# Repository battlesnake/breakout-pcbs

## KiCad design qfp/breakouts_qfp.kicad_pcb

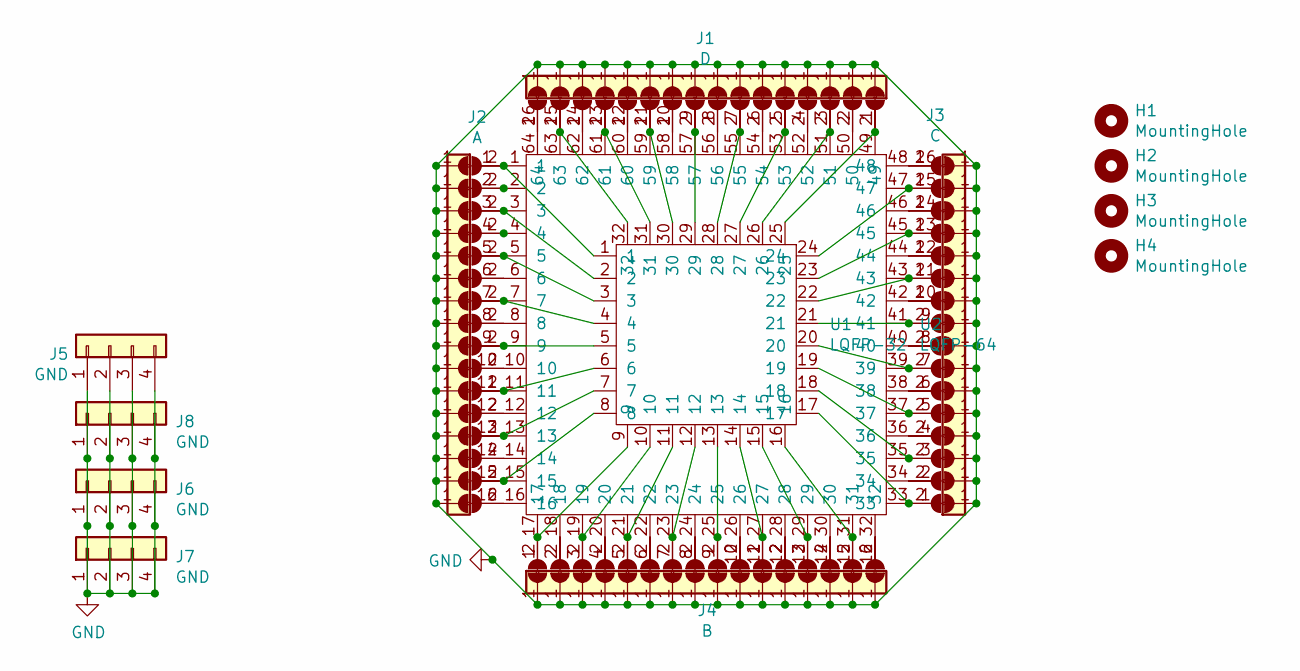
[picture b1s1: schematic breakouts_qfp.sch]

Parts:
H1, H2, H3, H4: MountingHole; MountingHole_2.2mm_M2
J1: D; PinHeader_1x16_P1.27mm_Vertical
J2: A; PinHeader_1x16_P1.27mm_Vertical
J3: C; PinHeader_1x16_P1.27mm_Vertical
J4: B; PinHeader_1x16_P1.27mm_Vertical
J5, J6, J7, J8: GND; PinHeader_1x04_P1.27mm_Vertical
JP1, JP2, JP3, JP4, JP5, JP6, JP7, JP8, JP9, JP10, JP11, JP12, JP13, JP14, JP15, JP16, JP17, JP18, JP19, JP20, JP21, JP22, JP23, JP24, JP25, JP26, JP27, JP28, JP29, JP30, JP31, JP32, JP33, JP34, JP35, JP36, JP37, JP38, JP39, JP40, JP41, JP42, JP43, JP44, JP45, JP46, JP47, JP48, JP49, JP50, JP51, JP52, JP53, JP54, JP55, JP56, JP57, JP58, JP59, JP60, JP61, JP62, JP63, JP64: SolderJumper_2_Open; C_0402_1005Metric_Pad0.74x0.62mm_HandSolder
U1: LQFP-32; LQFP-32_5x5mm_P0.5mm
U2: LQFP-64; LQFP-64_10x10mm_P0.5mm

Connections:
GND: J5.1, J5.2, J5.3, J5.4, J6.1, J6.2, J6.3, J6.4, J7.1, J7.2, J7.3, J7.4, J8.1, J8.2, J8.3, J8.4, JP1.1 (A), JP2.1 (A), JP3.1 (A), JP4.1 (A), JP5.1 (A), JP6.1 (A), JP7.1 (A), JP8.1 (A), JP9.1 (A), JP10.1 (A), JP11.1 (A), JP12.1 (A), JP13.1 (A), JP14.1 (A), JP15.1 (A), JP16.1 (A), JP17.1 (A), JP18.1 (A), JP19.1 (A), JP20.1 (A), JP21.1 (A), JP22.1 (A), JP23.1 (A), JP24.1 (A), JP25.1 (A), JP26.1 (A), JP27.1 (A), JP28.1 (A), JP29.1 (A), JP30.1 (A), JP31.1 (A), JP32.1 (A), JP33.1 (A), JP34.1 (A), JP35.1 (A), JP36.1 (A), JP37.1 (A), JP38.1 (A), JP39.1 (A), JP40.1 (A), JP41.1 (A), JP42.1 (A), JP43.1 (A), JP44.1 (A), JP45.1 (A), JP46.1 (A), JP47.1 (A), JP48.1 (A), JP49.1 (A), JP50.1 (A), JP51.1 (A), JP52.1 (A), JP53.1 (A), JP54.1 (A), JP55.1 (A), JP56.1 (A), JP57.1 (A), JP58.1 (A), JP59.1 (A), JP60.1 (A), JP61.1 (A), JP62.1 (A), JP63.1 (A), JP64.1 (A)
unnamed: J1.1, JP16.2 (B), U1.25, U2.49
unnamed: J1.2, JP15.2 (B), U2.50
unnamed: J1.3, JP14.2 (B), U1.26, U2.51
unnamed: J1.4, JP13.2 (B), U2.52
unnamed: J1.5, JP12.2 (B), U1.27, U2.53
unnamed: J1.6, JP11.2 (B), U2.54
unnamed: J1.7, JP10.2 (B), U1.28, U2.55
unnamed: J1.8, JP9.2 (B), U2.56
unnamed: J1.9, JP8.2 (B), U1.29, U2.57
unnamed: J1.10, JP7.2 (B), U2.58
unnamed: J1.11, JP6.2 (B), U1.30, U2.59
unnamed: J1.12, JP5.2 (B), U2.60
unnamed: J1.13, JP4.2 (B), U1.31, U2.61
unnamed: J1.14, JP3.2 (B), U2.62
unnamed: J1.15, JP2.2 (B), U1.32, U2.63
unnamed: J1.16, JP1.2 (B), U2.64
unnamed: J2.1, JP17.2 (B), U1.1, U2.1
unnamed: J2.2, JP19.2 (B), U2.2
unnamed: J2.3, JP21.2 (B), U1.2, U2.3
unnamed: J2.4, JP23.2 (B), U2.4
unnamed: J2.5, JP25.2 (B), U1.3, U2.5
unnamed: J2.6, JP27.2 (B), U2.6
unnamed: J2.7, JP29.2 (B), U1.4, U2.7
unnamed: J2.8, JP31.2 (B), U2.8
unnamed: J2.9, JP33.2 (B), U1.5, U2.9
unnamed: J2.10, JP35.2 (B), U2.10
unnamed: J2.11, JP37.2 (B), U1.6, U2.11
unnamed: J2.12, JP39.2 (B), U2.12
unnamed: J2.13, JP41.2 (B), U1.7, U2.13
unnamed: J2.14, JP43.2 (B), U2.14
unnamed: J2.15, JP45.2 (B), U1.8, U2.15
unnamed: J2.16, JP47.2 (B), U2.16
unnamed: J3.1, JP48.2 (B), U1.17, U2.33
unnamed: J3.2, JP46.2 (B), U2.34
unnamed: J3.3, JP44.2 (B), U1.18, U2.35
unnamed: J3.4, JP42.2 (B), U2.36
unnamed: J3.5, JP40.2 (B), U1.19, U2.37
unnamed: J3.6, JP38.2 (B), U2.38
unnamed: J3.7, JP36.2 (B), U1.20, U2.39
unnamed: J3.8, JP34.2 (B), U2.40
unnamed: J3.9, JP32.2 (B), U1.21, U2.41
unnamed: J3.10, JP30.2 (B), U2.42
unnamed: J3.11, JP28.2 (B), U1.22, U2.43
unnamed: J3.12, JP26.2 (B), U2.44
unnamed: J3.13, JP24.2 (B), U1.23, U2.45
unnamed: J3.14, JP22.2 (B), U2.46
unnamed: J3.15, JP20.2 (B), U1.24, U2.47
unnamed: J3.16, JP18.2 (B), U2.48
unnamed: J4.1, JP49.2 (B), U1.9, U2.17
unnamed: J4.2, JP50.2 (B), U2.18
unnamed: J4.3, JP51.2 (B), U1.10, U2.19
unnamed: J4.4, JP52.2 (B), U2.20
unnamed: J4.5, JP53.2 (B), U1.11, U2.21
unnamed: J4.6, JP54.2 (B), U2.22
unnamed: J4.7, JP55.2 (B), U1.12, U2.23
unnamed: J4.8, JP56.2 (B), U2.24
unnamed: J4.9, JP57.2 (B), U1.13, U2.25
unnamed: J4.10, JP58.2 (B), U2.26
unnamed: J4.11, JP59.2 (B), U1.14, U2.27
unnamed: J4.12, JP60.2 (B), U2.28
unnamed: J4.13, JP61.2 (B), U1.15, U2.29
unnamed: J4.14, JP62.2 (B), U2.30
unnamed: J4.15, JP63.2 (B), U1.16, U2.31
unnamed: J4.16, JP64.2 (B), U2.32

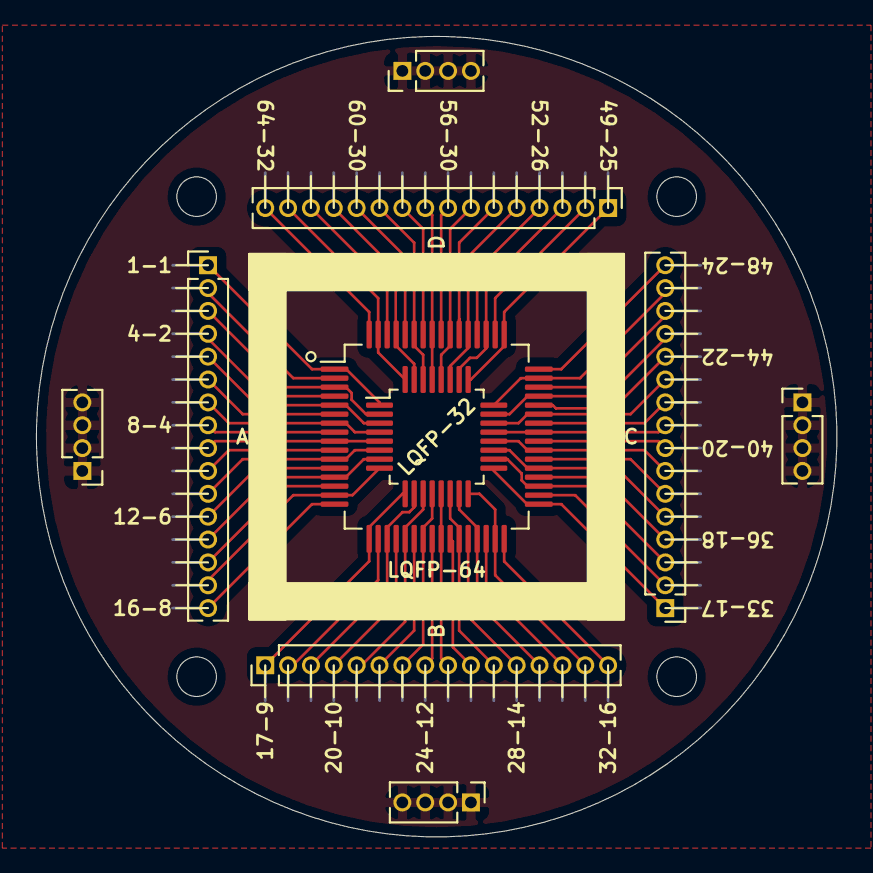
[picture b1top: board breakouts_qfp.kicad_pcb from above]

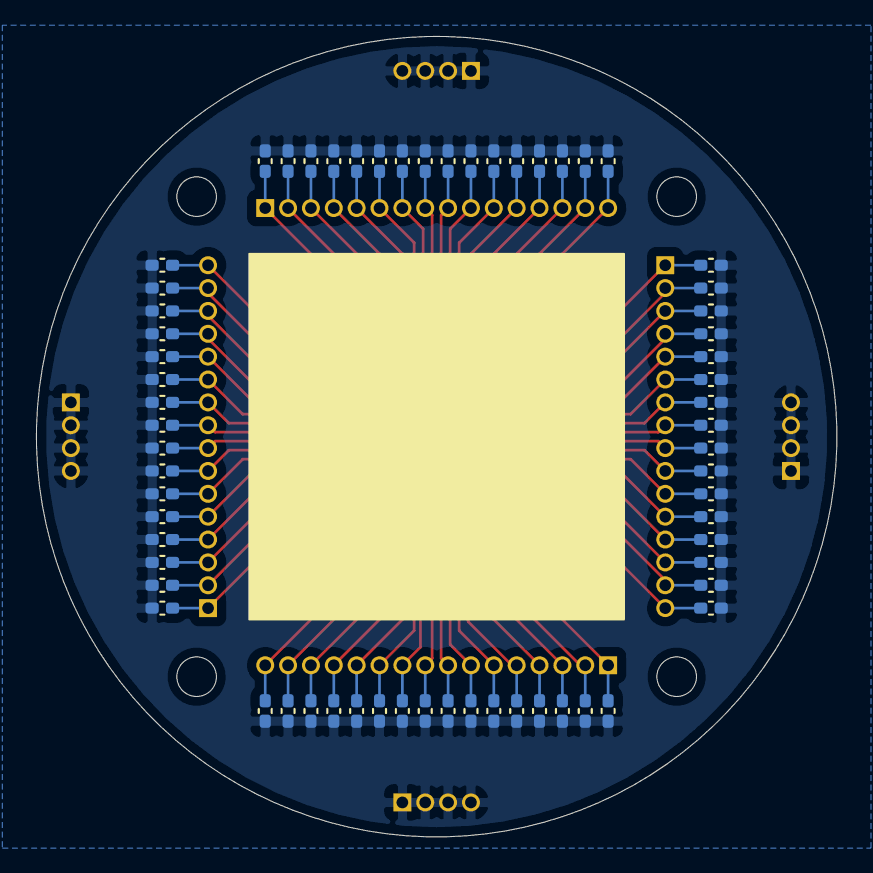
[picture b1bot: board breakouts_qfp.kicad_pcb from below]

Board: 2 copper layers, 44.5 x 44.5 mm, 78 parts (64 on the bottom side), 65 nets.

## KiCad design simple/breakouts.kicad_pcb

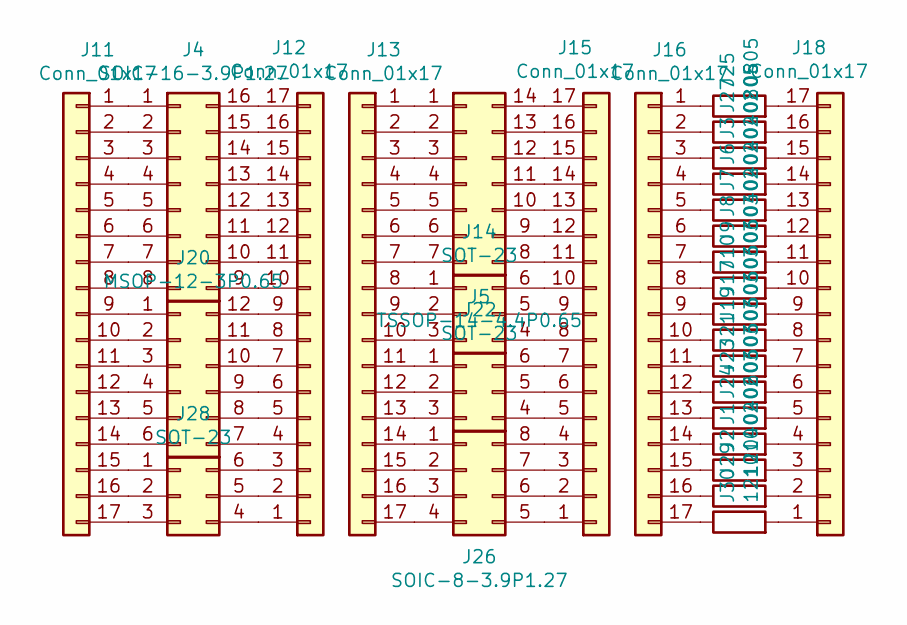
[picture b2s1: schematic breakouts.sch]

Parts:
J1, J2, J3, J6, J7, J8: 0402; D_0402_1005Metric_Pad0.77x0.64mm_HandSolder
J4: SOIC-16-3.9P1.27; SOIC-16_3.9x9.9mm_P1.27mm
J5: TSSOP-14-4.4P0.65; TSSOP-14-1EP_4.4x5mm_P0.65mm
J9, J10, J17, J19, J21, J23, J24: 0603; D_0603_1608Metric_Pad1.05x0.95mm_HandSolder
J11, J12, J13, J15, J16, J18: Conn_01x17; PinSocket_1x17_P2.54mm_Vertical
J14, J22, J28: SOT-23; SOT-23-6_Handsoldering
J20: MSOP-12-3P0.65; MSOP-12-1EP_3x4mm_P0.65mm_EP1.65x2.85mm
J25, J27: 0805; D_0805_2012Metric_Pad1.15x1.40mm_HandSolder
J26: SOIC-8-3.9P1.27; SOIC-8_3.9x4.9mm_P1.27mm
J29, J30: 1210; D_1210_3225Metric_Pad1.42x2.65mm_HandSolder

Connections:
unnamed: J1.1, J16.14
unnamed: J1.2, J18.4
unnamed: J10.1, J16.8
unnamed: J10.2, J18.10
unnamed: J4.1, J11.1
unnamed: J4.2, J11.2
unnamed: J4.3, J11.3
unnamed: J4.4, J11.4
unnamed: J4.5, J11.5
unnamed: J4.6, J11.6
unnamed: J4.7, J11.7
unnamed: J4.8, J11.8
unnamed: J11.9, J20.1
unnamed: J11.10, J20.2
unnamed: J11.11, J20.3
unnamed: J11.12, J20.4
unnamed: J11.13, J20.5
unnamed: J11.14, J20.6
unnamed: J11.15, J28.1
unnamed: J11.16, J28.2
unnamed: J11.17, J28.3
unnamed: J12.1, J28.4
unnamed: J12.2, J28.5
unnamed: J12.3, J28.6
unnamed: J12.4, J20.7
unnamed: J12.5, J20.8
unnamed: J12.6, J20.9
unnamed: J12.7, J20.10
unnamed: J12.8, J20.11
unnamed: J12.9, J20.12
unnamed: J4.9, J12.10
unnamed: J4.10, J12.11
unnamed: J4.11, J12.12
unnamed: J4.12, J12.13
unnamed: J4.13, J12.14
unnamed: J4.14, J12.15
unnamed: J4.15, J12.16
unnamed: J4.16, J12.17
unnamed: J5.1, J13.1
unnamed: J5.2, J13.2
unnamed: J5.3, J13.3
unnamed: J5.4, J13.4
unnamed: J5.5, J13.5
unnamed: J5.6, J13.6
unnamed: J5.7, J13.7
unnamed: J13.8, J14.1
unnamed: J13.9, J14.2
unnamed: J13.10, J14.3
unnamed: J13.11, J22.1
unnamed: J13.12, J22.2
unnamed: J13.13, J22.3
unnamed: J13.14, J26.1
unnamed: J13.15, J26.2
unnamed: J13.16, J26.3
unnamed: J13.17, J26.4
unnamed: J14.4, J15.8
unnamed: J14.5, J15.9
unnamed: J14.6, J15.10
unnamed: J15.1, J26.5
unnamed: J15.2, J26.6
unnamed: J15.3, J26.7
unnamed: J15.4, J26.8
unnamed: J15.5, J22.4
unnamed: J15.6, J22.5
unnamed: J15.7, J22.6
unnamed: J5.8, J15.11
unnamed: J5.9, J15.12
unnamed: J5.10, J15.13
unnamed: J5.11, J15.14
unnamed: J5.12, J15.15
unnamed: J5.13, J15.16
unnamed: J5.14, J15.17
unnamed: J16.1, J25.1
unnamed: J16.2, J27.1
unnamed: J3.1, J16.3
unnamed: J6.1, J16.4
unnamed: J7.1, J16.5
unnamed: J8.1, J16.6
unnamed: J9.1, J16.7
unnamed: J16.9, J17.1
unnamed: J16.10, J19.1
unnamed: J16.11, J21.1
unnamed: J16.12, J23.1
unnamed: J16.13, J24.1
unnamed: J2.1, J16.15
unnamed: J16.16, J29.1
unnamed: J16.17, J30.1
unnamed: J17.2, J18.9
unnamed: J18.1, J30.2
unnamed: J18.2, J29.2
unnamed: J2.2, J18.3
unnamed: J18.5, J24.2
unnamed: J18.6, J23.2
unnamed: J18.7, J21.2
unnamed: J18.8, J19.2
unnamed: J9.2, J18.11
unnamed: J8.2, J18.12
unnamed: J7.2, J18.13
unnamed: J6.2, J18.14
unnamed: J3.2, J18.15
unnamed: J18.16, J27.2
unnamed: J18.17, J25.2

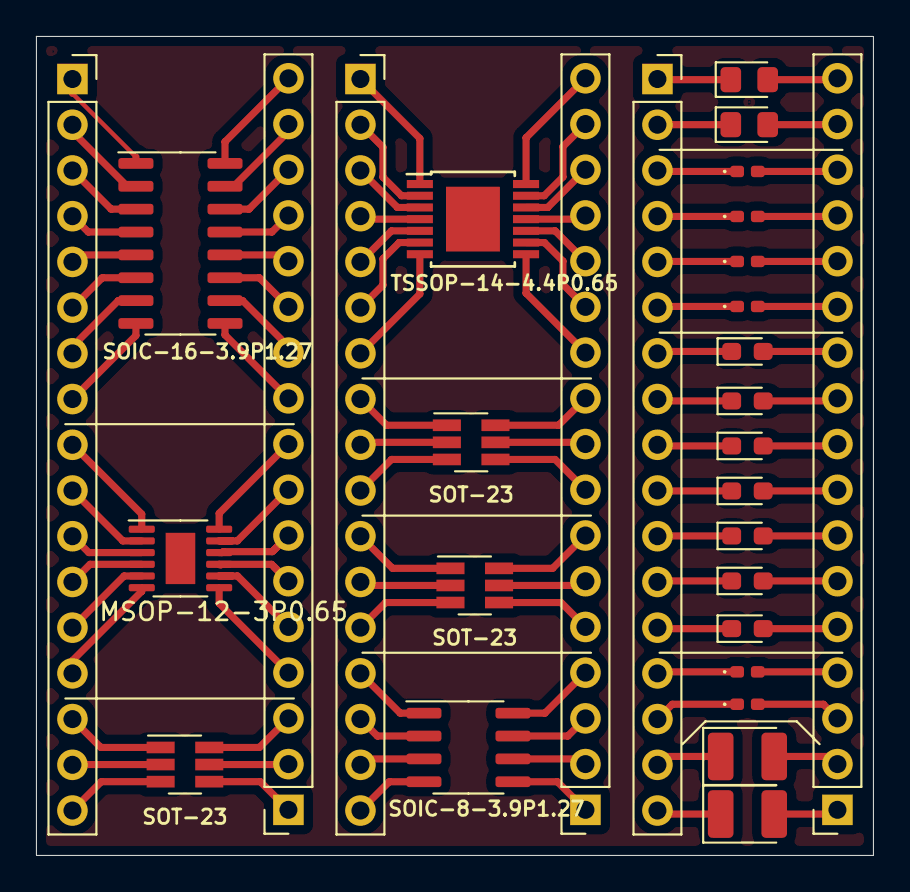
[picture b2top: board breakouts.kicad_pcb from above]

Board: 2 copper layers, 46.5 x 45.5 mm, 30 parts (0 on the bottom side), 102 nets.

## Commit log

2021-10-21 initial
